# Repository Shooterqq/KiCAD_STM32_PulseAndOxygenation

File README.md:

# KiCAD_STM32_PulseAndOxygenation
This is my projest made in KiCAD using STM32F105.
It is builded in my free time for project with pulse and oxygenation sensor (MAN30101) and OLED screen.

3D viev:

Electrical scheme:

PCB layers:

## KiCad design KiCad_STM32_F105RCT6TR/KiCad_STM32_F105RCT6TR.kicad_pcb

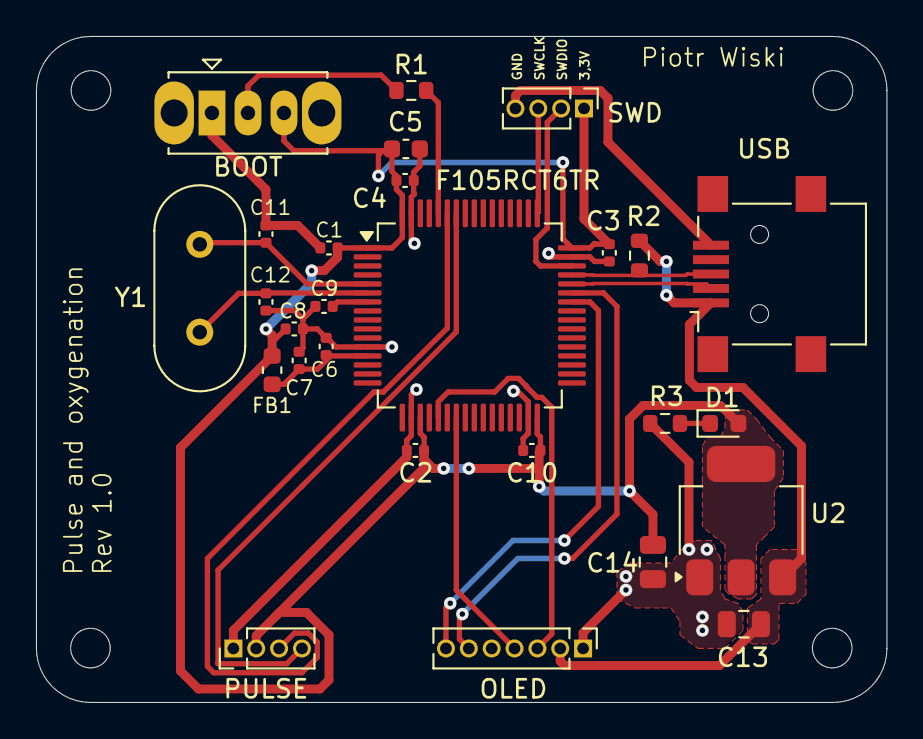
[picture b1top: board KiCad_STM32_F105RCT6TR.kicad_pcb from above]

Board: 2 copper layers, 47.2 x 37.0 mm, 31 parts (0 on the bottom side), 20 nets.

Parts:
BOOT: SW_SPDT; SW_Slide_SPDT_Straight_CK_OS102011MS2Q
C1, C2, C3, C4, C9, C10: 100n; C_0402_1005Metric
C5: 10u; C_0603_1608Metric
C6: 10n; C_0402_1005Metric
C7, C8: 1u; C_0402_1005Metric
C11, C12: 22p; C_0402_1005Metric
C13, C14: 22u; C_0805_2012Metric
D1: RED_LED; LED_0603_1608Metric
F105RCT6TR: STM32F105RCT6TR; LQFP-64_10x10mm_P0.5mm
FB1: 120R; L_0603_1608Metric
H1, H2, H3, H4: MountingHole; MountingHole_2.2mm_M2
OLED: Conn_OLED; PinHeader_1x07_P1.27mm_Vertical
PULSE: Conn_MAX; PinHeader_1x04_P1.27mm_Vertical
R1: 10k; R_0603_1608Metric
R2, R3: 1k5; R_0603_1608Metric
SWD: Conn_SWD; PinHeader_1x04_P1.27mm_Vertical
U2: AMS1117-3.3; SOT-223-3_TabPin2
USB: USB_B_Micro; USB_Mini-B_Lumberg_2486_01_Horizontal
Y1: 16MHz; Crystal_HC49-4H_Vertical

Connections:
+3.3V: BOOT.3 (C), C1.1, C2.1, C3.1, C4.1, C5.1, C8.1, C10.1, C14.1, D1.2 (A), F105RCT6TR.1 (VBAT), F105RCT6TR.19 (VDD), F105RCT6TR.32 (VDD), F105RCT6TR.48 (VDD), F105RCT6TR.64 (VDD), FB1.2, PULSE.2, SWD.1, U2.2 (VO)
+3.3VA: C6.1, C7.1, F105RCT6TR.13 (VDDA), FB1.1
/HSE_IN: C11.1, F105RCT6TR.5 (PD0), Y1.1
/HSE_OUT: C12.1, F105RCT6TR.6 (PD1), Y1.2
/I2C1_SCL: F105RCT6TR.58 (PB6), PULSE.4
/I2C1_SDA: F105RCT6TR.59 (PB7), PULSE.3
/NRST: C9.1, F105RCT6TR.7 (NRST)
/OLED_CS: F105RCT6TR.42 (PA9), OLED.7
/OLED_DC: F105RCT6TR.43 (PA10), OLED.6
/SPI1_MOSI: F105RCT6TR.23 (PA7), OLED.4
/SPI1_SCK: F105RCT6TR.21 (PA5), OLED.3
/SWCLK: F105RCT6TR.49 (PA14), SWD.3
/SWDIO: F105RCT6TR.46 (PA13), SWD.2
/USB_D+: F105RCT6TR.45 (PA12), R2.2, USB.3 (D+)
/USB_D-: F105RCT6TR.44 (PA11), USB.2 (D-)
GND: BOOT.1 (A), C1.2, C2.2, C3.2, C4.2, C5.2, C6.2, C7.2, C8.2, C9.2, C10.2, C11.2, C12.2, C13.2, C14.2, F105RCT6TR.12 (VSSA), F105RCT6TR.18 (VSS), F105RCT6TR.31 (VSS), F105RCT6TR.47 (VSS), F105RCT6TR.63 (VSS), OLED.1, OLED.5, PULSE.1, R3.1, SWD.4, U2.1 (GND), USB.5 (GND)
unnamed: D1.1 (K), R3.2
unnamed: BOOT.2 (B), R1.1
unnamed: F105RCT6TR.60 (BOOT0), R1.2
VBUS: C13.1, OLED.2, R2.1, U2.3 (VI), USB.1 (VBUS)

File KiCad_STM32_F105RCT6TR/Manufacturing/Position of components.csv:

Ref,Val,Package,PosX,PosY,Rot,Side
"BOOT","SW_SPDT","SW_Slide_SPDT_Straight_CK_OS102011MS2Q",93.000000,-54.250000,0.000000,top
"C1","100n","C_0402_1005Metric",99.500000,-61.750000,180.000000,top
"C2","100n","C_0402_1005Metric",104.305000,-73.000000,180.000000,top
"C3","100n","C_0402_1005Metric",115.075000,-62.020000,-90.000000,top
"C4","100n","C_0402_1005Metric",103.730000,-58.000000,0.000000,top
"C5","10u","C_0603_1608Metric",103.775000,-56.250000,0.000000,top
"C6","10n","C_0402_1005Metric",99.345000,-67.225000,90.000000,top
"C7","1u","C_0402_1005Metric",97.845000,-68.000000,90.000000,top
"C8","1u","C_0402_1005Metric",97.575000,-66.250000,0.000000,top
"C9","100n","C_0402_1005Metric",99.230000,-65.000000,180.000000,top
"C10","100n","C_0402_1005Metric",110.770000,-73.000000,180.000000,top
"C11","22p","C_0402_1005Metric",96.000000,-60.980000,90.000000,top
"C12","22p","C_0402_1005Metric",96.000000,-64.750000,-90.000000,top
"C13","22u","C_0805_2012Metric",122.550000,-82.650000,180.000000,top
"C14","22u","C_0805_2012Metric",117.500000,-79.200000,-90.000000,top
"D1","RED_LED","LED_0603_1608Metric",121.462500,-71.500000,0.000000,top
"F105RCT6TR","STM32F105RCT6TR","LQFP-64_10x10mm_P0.5mm",107.325000,-65.500000,0.000000,top
"FB1","120R","L_0603_1608Metric",96.345000,-68.537500,90.000000,top
"JSWD","Conn_SWD","PinHeader_1x04_P1.27mm_Vertical",113.670000,-54.000000,-90.000000,top
"OLED","Conn_OLED","PinHeader_1x07_P1.27mm_Vertical",113.620000,-84.000000,-90.000000,top
"PULSE","Conn_MAX","PinHeader_1x04_P1.27mm_Vertical",94.190000,-84.000000,90.000000,top
"R1","10k","R_0603_1608Metric",104.075000,-53.000000,0.000000,top
"R2","1k5","R_0603_1608Metric",116.750000,-62.175000,-90.000000,top
"R3","1k5","R_0603_1608Metric",118.175000,-71.500000,0.000000,top
"U2","AMS1117-3.3","SOT-223-3_TabPin2",122.400000,-76.900000,90.000000,top
"USB","USB_B_Micro","USB_Mini-B_Lumberg_2486_01_Horizontal",123.425000,-63.200000,90.000000,top
"Y1","16MHz","Crystal_HC49-4H_Vertical",92.325000,-61.550000,-90.000000,top

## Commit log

2024-06-15 Added project
    Added project:
    - gerber files
    - BOM files
    - Position of components
    - Electrical scheme
    - PCB layers
2024-06-15 Added 3D_Viev
